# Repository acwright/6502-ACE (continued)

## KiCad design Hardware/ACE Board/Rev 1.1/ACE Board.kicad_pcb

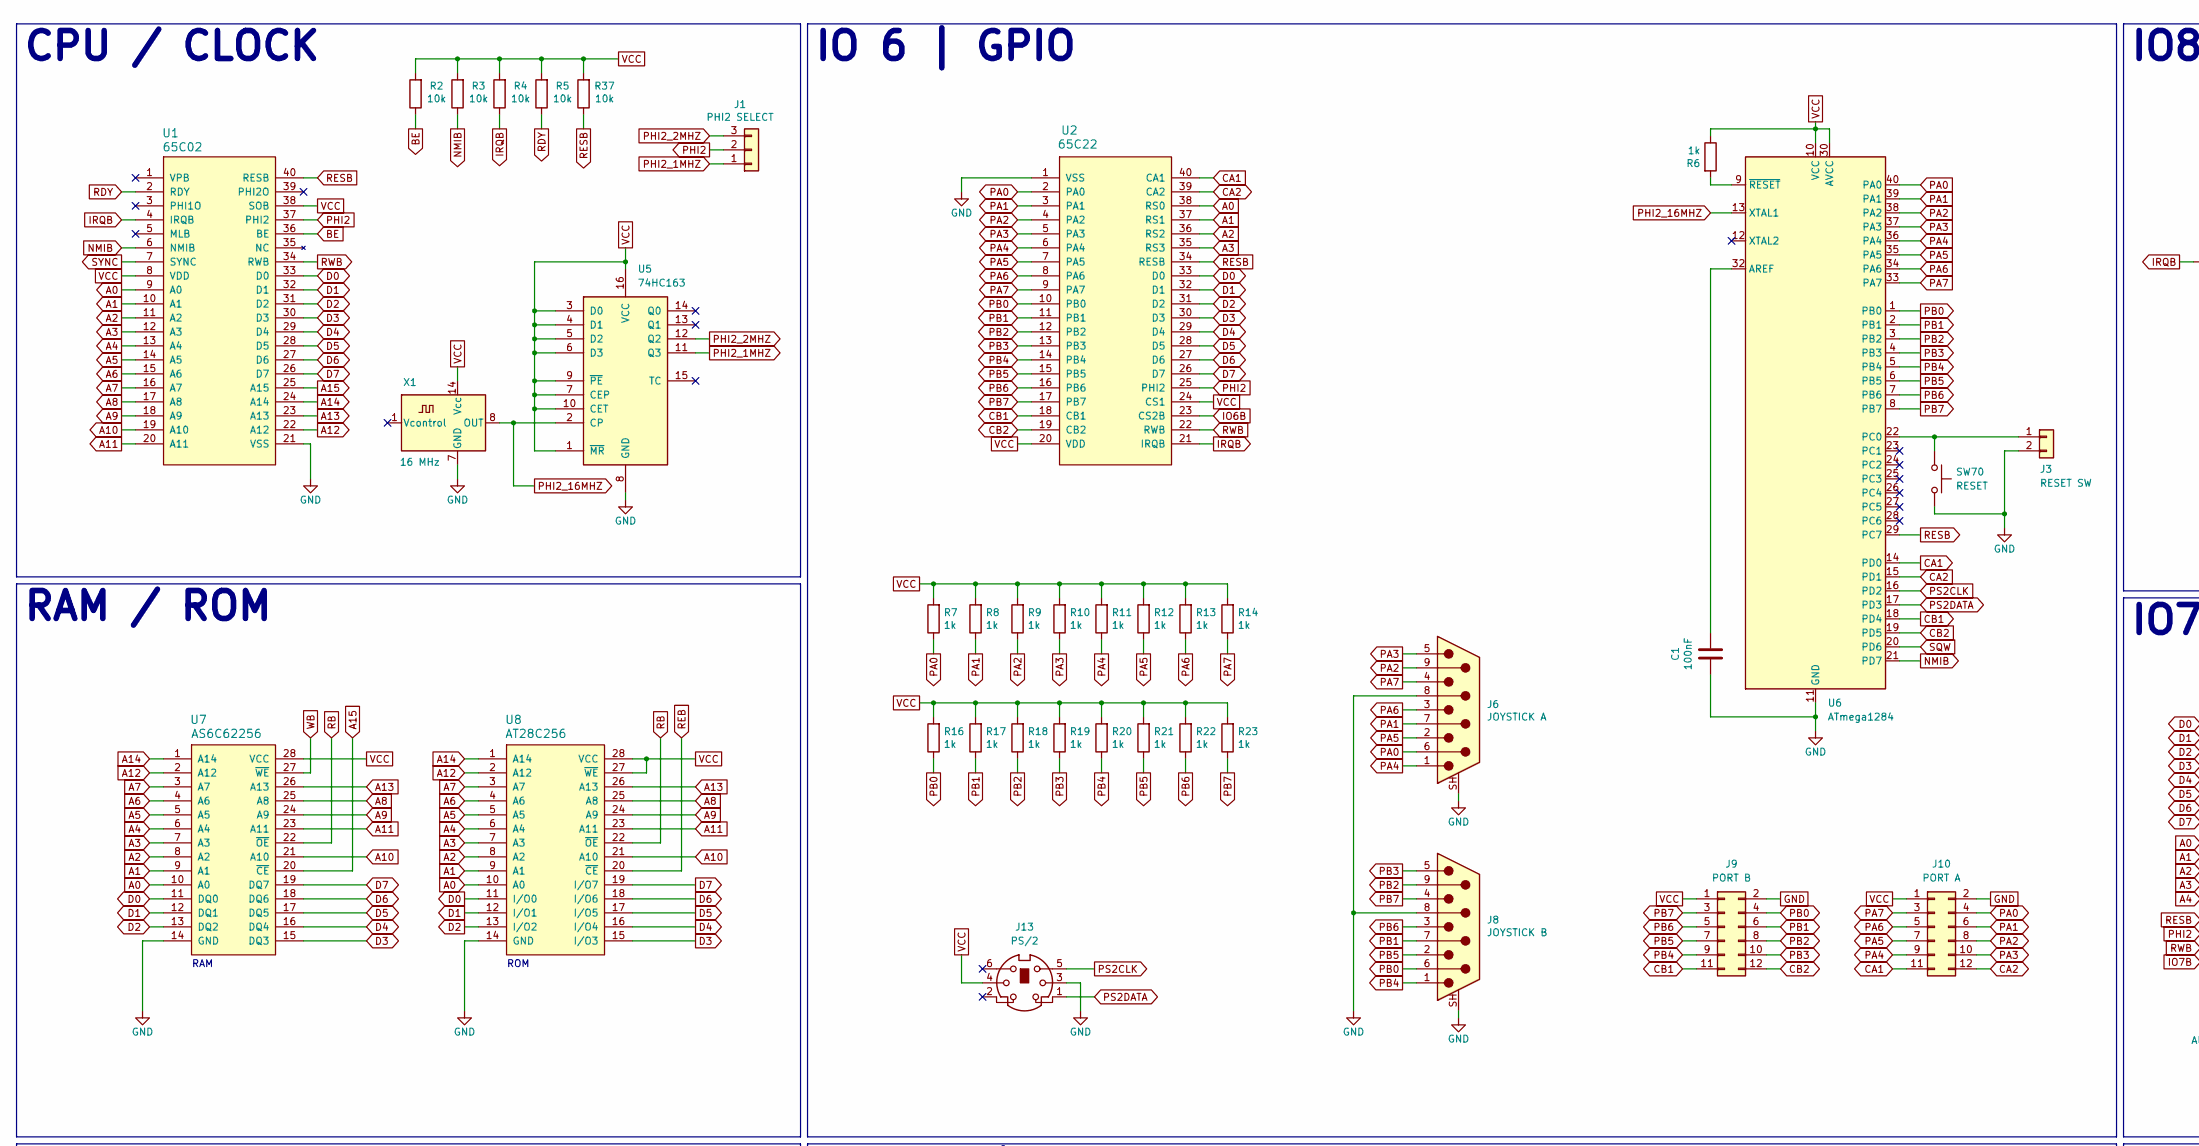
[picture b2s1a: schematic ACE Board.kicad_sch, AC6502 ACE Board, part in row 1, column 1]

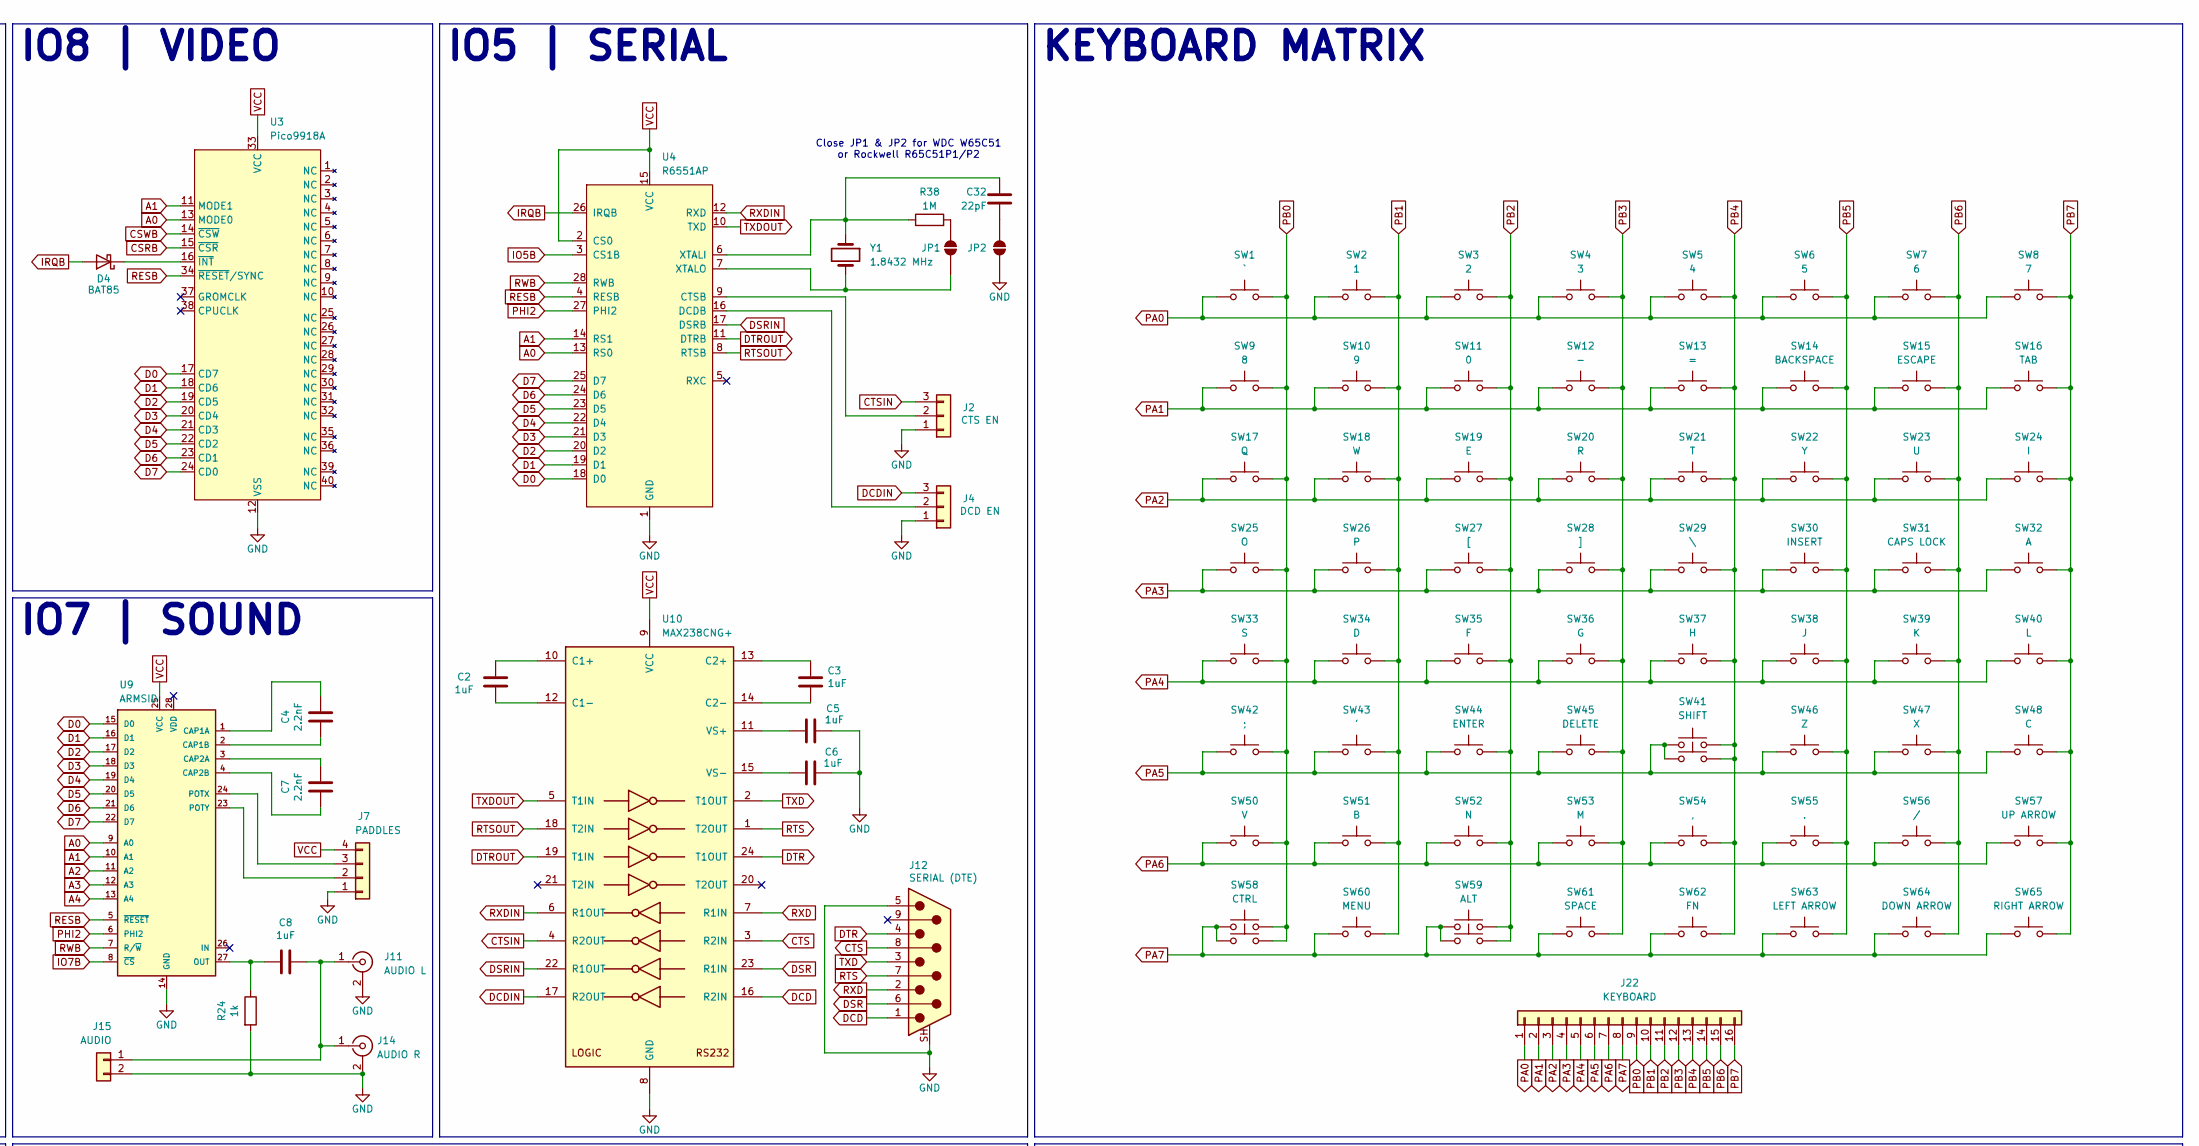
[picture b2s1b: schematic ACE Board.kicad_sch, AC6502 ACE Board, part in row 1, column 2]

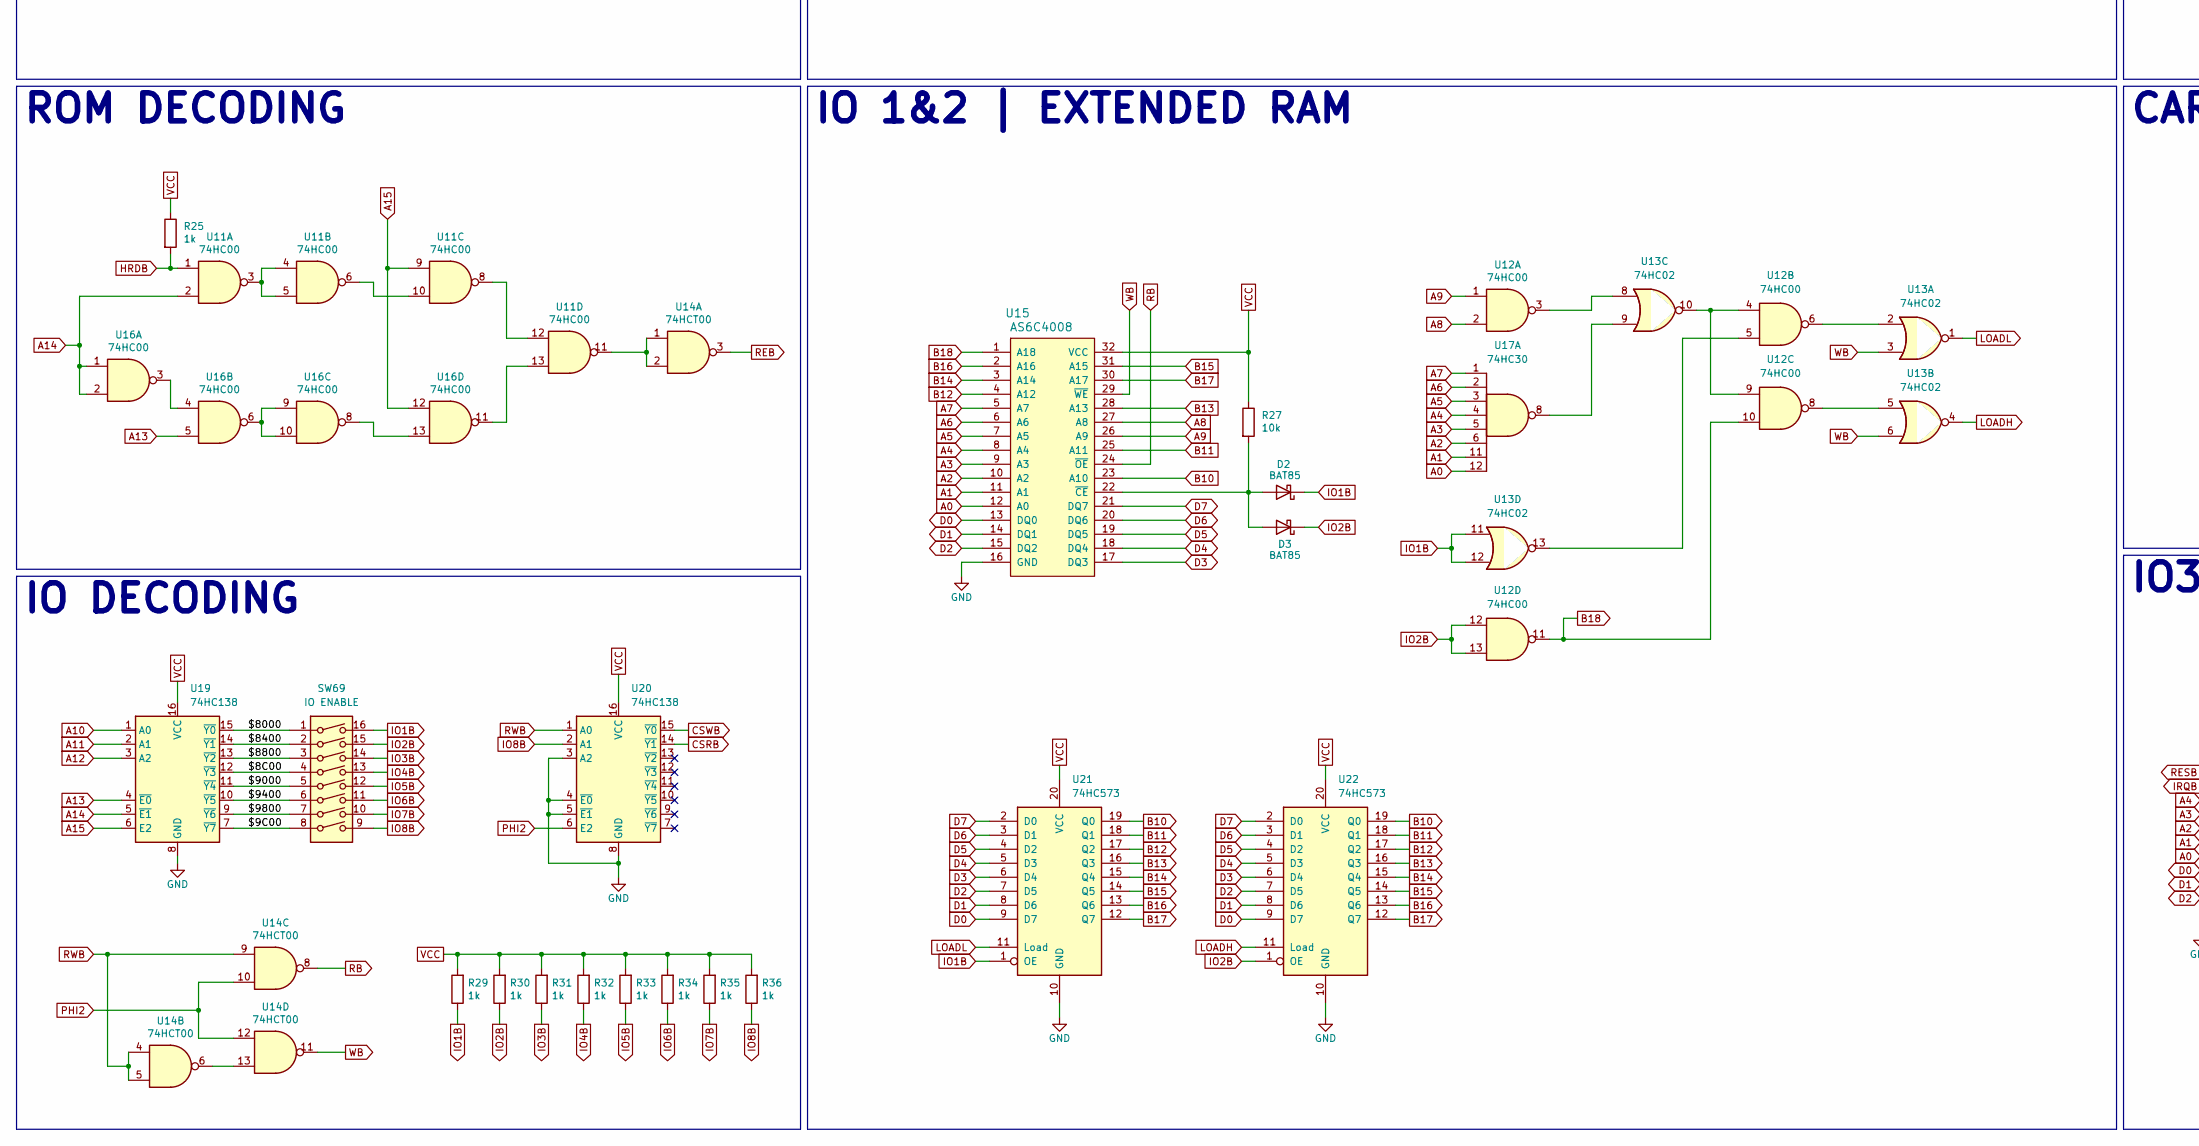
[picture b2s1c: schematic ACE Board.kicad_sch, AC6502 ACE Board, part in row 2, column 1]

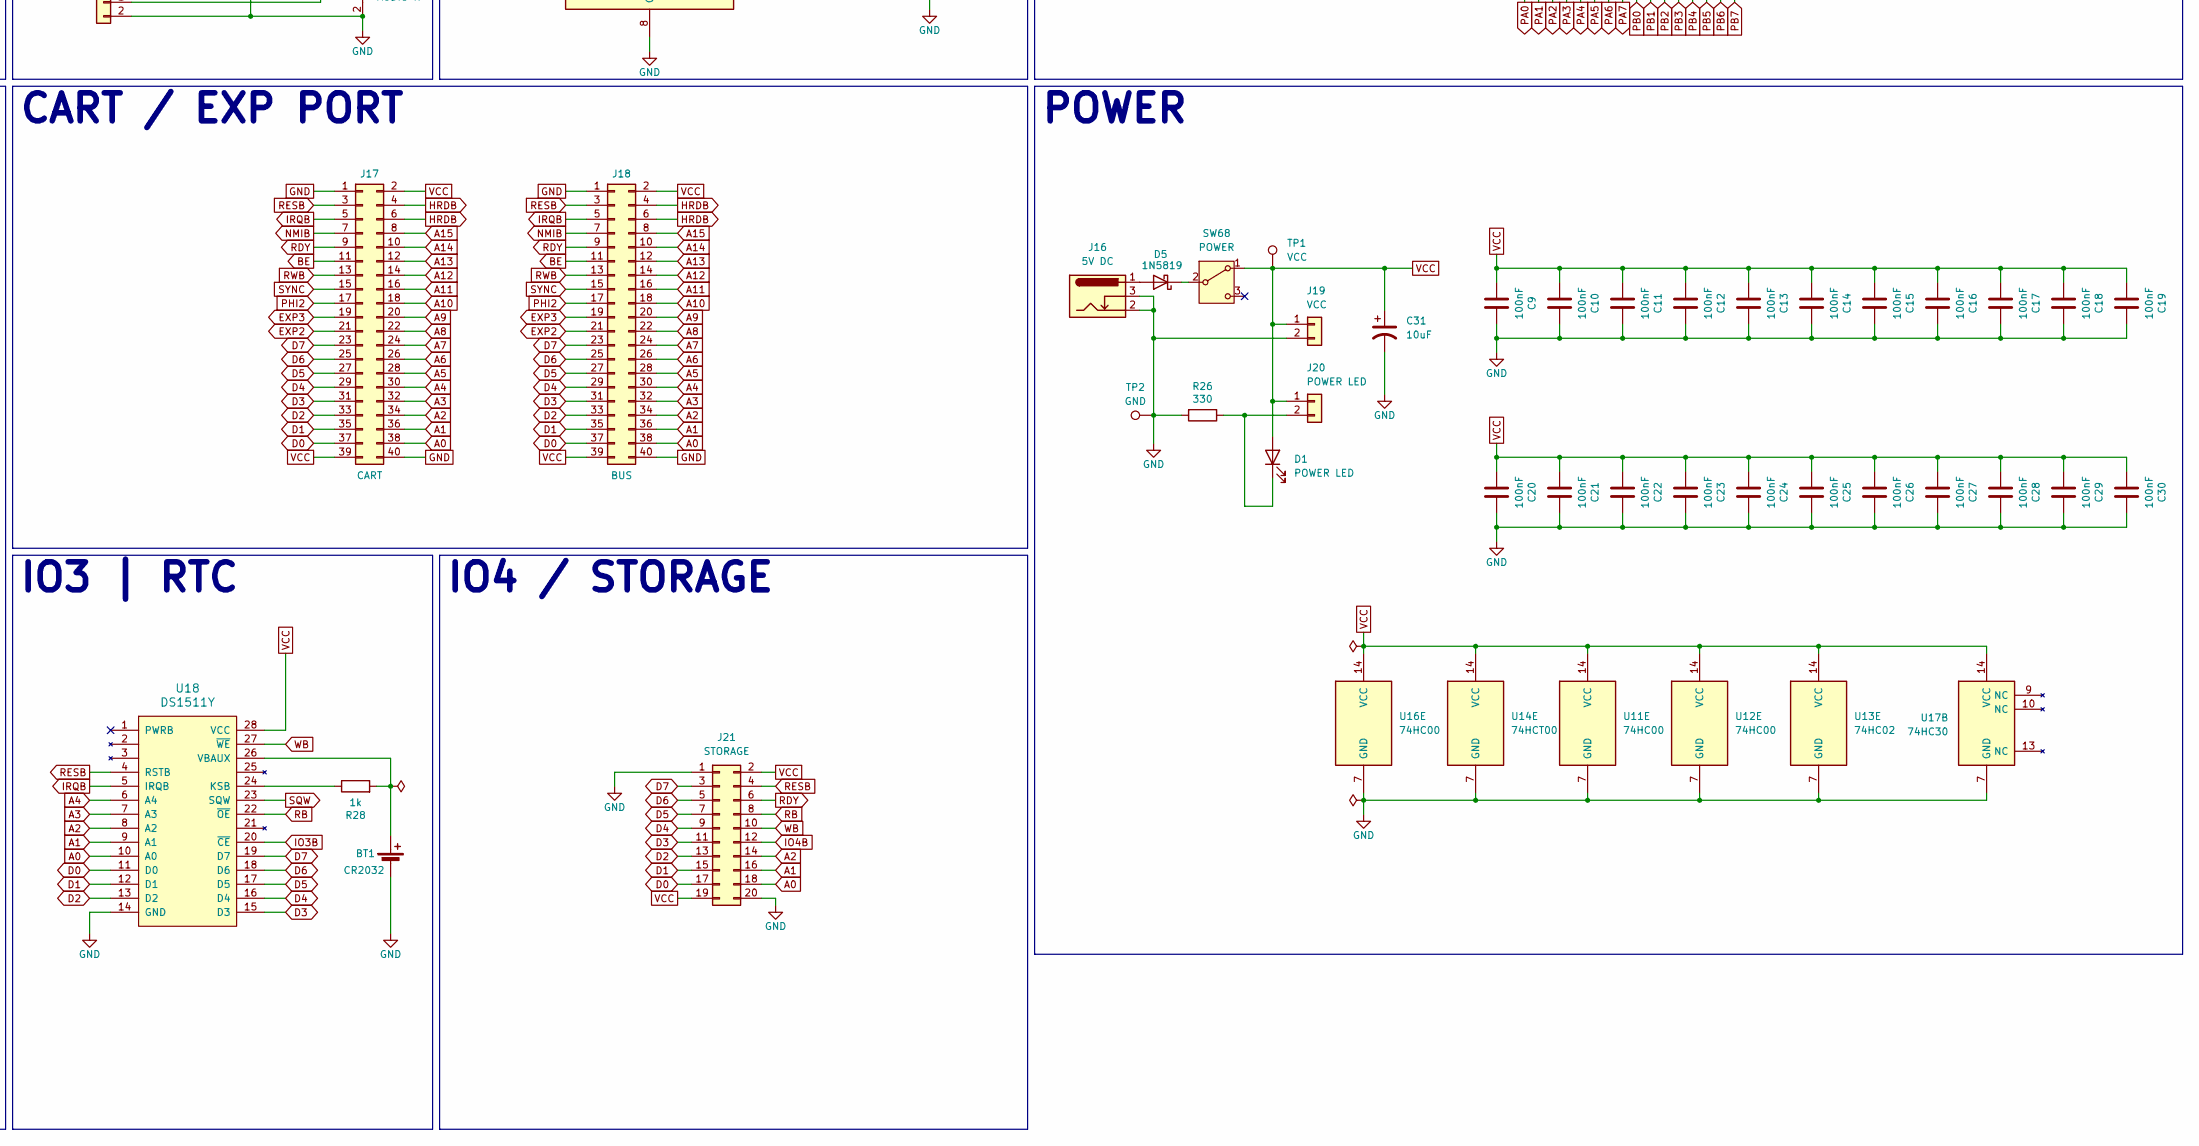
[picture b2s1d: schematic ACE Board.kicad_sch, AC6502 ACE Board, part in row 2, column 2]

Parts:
BT1: CR2032; CR2032 Holder Numbered; Digikey 343-BAT-HLD-001-THM-TRCT-ND
C1, C9, C10, C11, C12, C13, C14, C15, C16, C17, C18, C19, C20, C21, C22, C23, C24, C25, C26, C27, C28, C29, C30: 100nF; C_Disc_D5.0mm_W2.5mm_P2.50mm; Digikey 478-3187-ND
C2, C3, C5, C6, C8: 1uF; C_Disc_D5.0mm_W2.5mm_P2.50mm; Digikey 478-7667-ND
C4, C7: 2.2nF; C_Disc_D5.0mm_W2.5mm_P2.50mm; Digikey 478-11698-ND
C31: 10uF; CP_Radial_D4.0mm_P1.50mm; Digikey P14482-ND
C32: 22pF; C_Disc_D5.0mm_W2.5mm_P2.50mm; Digikey 478-4846-ND
D1: POWER LED; LED_D3.0mm; Digikey 732-5008-ND
D2, D3, D4: BAT85; D_DO-35_SOD27_P7.62mm_Horizontal; Digikey BAT85SCT-ND
D5: 1N5819; D_DO-41_SOD81_P10.16mm_Horizontal; Digikey 1N5819-E3/54GICT-ND
J1: PHI2 SELECT; PinHeader_1x03_P2.54mm_Vertical; Digikey S1011EC-40-ND
J2: CTS EN; PinHeader_1x03_P2.54mm_Vertical; Digikey S1011EC-40-ND
J3: RESET SW; PinHeader_1x02_P2.54mm_Vertical; Digikey S1011EC-40-ND
J4: DCD EN; PinHeader_1x03_P2.54mm_Vertical; Digikey S1011EC-40-ND
J6: JOYSTICK A; DSUB-9_Pins_Horizontal_P2.77x2.84mm_EdgePinOffset7.70mm_Hou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; Digikey 609-1481-ND
J7: PADDLES; PinHeader_1x04_P2.54mm_Vertical; Digikey S1011EC-40-ND
J8: JOYSTICK B; DSUB-9_Pins_Horizontal_P2.77x2.84mm_EdgePinOffset7.70mm_Hou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; Digikey 609-1481-ND
J9: PORT B; 6502 GPIO Connector; Digikey 2057-BHR-12-VUA-ND
J10: PORT A; 6502 GPIO Connector; Digikey 2057-BHR-12-VUA-ND
J11: AUDIO L; RCA Jack White; Digikey PJRAN1X1U02X-ND
J12: SERIAL (DTE); DSUB-9_Pins_Horizontal_P2.77x2.84mm_EdgePinOffset7.70mm_Hou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; Digikey 609-1481-ND
J13: PS/2; PS2 Jack; Mouser 806-KMDGX-6S-BS
J14: AUDIO R; RCA Jack White; Digikey PJRAN1X1U03X-ND
J15: AUDIO; PinHeader_1x02_P2.54mm_Vertical; Digikey S1011EC-40-ND
J16: 5V DC; BarrelJack_Horizontal; Digikey CP-102AH-ND
J17: CART; 6502 Card Slot; Digikey A31723-ND
J18: BUS; 6502 Bus Connector; Digikey 732-5401-ND
J19: VCC; PinHeader_1x02_P2.54mm_Vertical; Digikey S1011EC-40-ND
J20: POWER LED; PinHeader_1x02_P2.54mm_Vertical; Digikey S1011EC-40-ND
J21: STORAGE; PinSocket_2x10_P2.54mm_Horizontal; Digikey S5563-ND
J22: KEYBOARD; PinHeader_1x16_P2.00mm_Vertical; Digikey 2057-2PH1-16-UA-ND
JP1, JP2: SolderJumper_2_Open; SolderJumper-2_P1.3mm_Open_RoundedPad1.0x1.5mm
R2, R3, R4, R5, R27, R37: 10k; R_Axial_DIN0204_L3.6mm_D1.6mm_P5.08mm_Horizontal; Digikey 13-MFR-12FTF52-10KCT-ND
R6, R7, R8, R9, R10, R11, R12, R13, R14, R16, R17, R18, R19, R20, R21, R22, R23, R24, R25, R28, R29, R30, R31, R32, R33, R34, R35, R36: 1k; R_Axial_DIN0204_L3.6mm_D1.6mm_P5.08mm_Horizontal; Digikey 13-MFR-12FTF52-1KCT-ND
R26: 330; R_Axial_DIN0204_L3.6mm_D1.6mm_P5.08mm_Horizontal; Digikey 13-MFR-12FTF52-330RCT-ND
R38: 1M; R_Axial_DIN0204_L3.6mm_D1.6mm_P5.08mm_Horizontal; Digikey 13-MFR-12FTF52-1MCT-ND
SW1: `; SW_Cherry_MX_1.00u_PCB; Digikey 1644-MX2A-E1NA-ND
SW2: 1; SW_Cherry_MX_1.00u_PCB; Digikey 1644-MX2A-E1NA-ND
SW3: 2; SW_Cherry_MX_1.00u_PCB; Digikey 1644-MX2A-E1NA-ND
SW4: 3; SW_Cherry_MX_1.00u_PCB; Digikey 1644-MX2A-E1NA-ND
SW5: 4; SW_Cherry_MX_1.00u_PCB; Digikey 1644-MX2A-E1NA-ND
SW6: 5; SW_Cherry_MX_1.00u_PCB; Digikey 1644-MX2A-E1NA-ND
SW7: 6; SW_Cherry_MX_1.00u_PCB; Digikey 1644-MX2A-E1NA-ND
SW8: 7; SW_Cherry_MX_1.00u_PCB; Digikey 1644-MX2A-E1NA-ND
SW9: 8; SW_Cherry_MX_1.00u_PCB; Digikey 1644-MX2A-E1NA-ND
SW10: 9; SW_Cherry_MX_1.00u_PCB; Digikey 1644-MX2A-E1NA-ND
SW11: 0; SW_Cherry_MX_1.00u_PCB; Digikey 1644-MX2A-E1NA-ND
SW12: -; SW_Cherry_MX_1.00u_PCB; Digikey 1644-MX2A-E1NA-ND
SW13: =; SW_Cherry_MX_1.00u_PCB; Digikey 1644-MX2A-E1NA-ND
SW14: BACKSPACE; SW_Cherry_MX_2.00u_PCB; Digikey 1644-MX2A-E1NA-ND
SW15: ESCAPE; SW_Cherry_MX_1.00u_PCB; Digikey 1644-MX2A-E1NA-ND
SW16: TAB; SW_Cherry_MX_1.50u_PCB; Digikey 1644-MX2A-E1NA-ND
SW17: Q; SW_Cherry_MX_1.00u_PCB; Digikey 1644-MX2A-E1NA-ND
SW18: W; SW_Cherry_MX_1.00u_PCB; Digikey 1644-MX2A-E1NA-ND
SW19: E; SW_Cherry_MX_1.00u_PCB; Digikey 1644-MX2A-E1NA-ND
SW20: R; SW_Cherry_MX_1.00u_PCB; Digikey 1644-MX2A-E1NA-ND
SW21: T; SW_Cherry_MX_1.00u_PCB; Digikey 1644-MX2A-E1NA-ND
SW22: Y; SW_Cherry_MX_1.00u_PCB; Digikey 1644-MX2A-E1NA-ND
SW23: U; SW_Cherry_MX_1.00u_PCB; Digikey 1644-MX2A-E1NA-ND
SW24: I; SW_Cherry_MX_1.00u_PCB; Digikey 1644-MX2A-E1NA-ND
SW25: O; SW_Cherry_MX_1.00u_PCB; Digikey 1644-MX2A-E1NA-ND
SW26: P; SW_Cherry_MX_1.00u_PCB; Digikey 1644-MX2A-E1NA-ND
SW27: [; SW_Cherry_MX_1.00u_PCB; Digikey 1644-MX2A-E1NA-ND
SW28: ]; SW_Cherry_MX_1.00u_PCB; Digikey 1644-MX2A-E1NA-ND
SW29: \; SW_Cherry_MX_1.50u_PCB; Digikey 1644-MX2A-E1NA-ND
SW30: INSERT; SW_Cherry_MX_1.00u_PCB; Digikey 1644-MX2A-E1NA-ND
SW31: CAPS LOCK; SW_Cherry_MX_1.75u_PCB; Digikey 1644-MX2A-E1NA-ND
SW32: A; SW_Cherry_MX_1.00u_PCB; Digikey 1644-MX2A-E1NA-ND
SW33: S; SW_Cherry_MX_1.00u_PCB; Digikey 1644-MX2A-E1NA-ND
SW34: D; SW_Cherry_MX_1.00u_PCB; Digikey 1644-MX2A-E1NA-ND
SW35: F; SW_Cherry_MX_1.00u_PCB; Digikey 1644-MX2A-E1NA-ND
SW36: G; SW_Cherry_MX_1.00u_PCB; Digikey 1644-MX2A-E1NA-ND
SW37: H; SW_Cherry_MX_1.00u_PCB; Digikey 1644-MX2A-E1NA-ND
SW38: J; SW_Cherry_MX_1.00u_PCB; Digikey 1644-MX2A-E1NA-ND
SW39: K; SW_Cherry_MX_1.00u_PCB; Digikey 1644-MX2A-E1NA-ND
SW40: L; SW_Cherry_MX_1.00u_PCB; Digikey 1644-MX2A-E1NA-ND
SW41, SW49: SHIFT; SW_Cherry_MX_2.25u_PCB; Digikey 1644-MX2A-E1NA-ND
SW42: ;; SW_Cherry_MX_1.00u_PCB; Digikey 1644-MX2A-E1NA-ND
SW43: '; SW_Cherry_MX_1.00u_PCB; Digikey 1644-MX2A-E1NA-ND
SW44: ENTER; SW_Cherry_MX_2.25u_PCB; Digikey 1644-MX2A-E1NA-ND
SW45: DELETE; SW_Cherry_MX_1.00u_PCB; Digikey 1644-MX2A-E1NA-ND
SW46: Z; SW_Cherry_MX_1.00u_PCB; Digikey 1644-MX2A-E1NA-ND
SW47: X; SW_Cherry_MX_1.00u_PCB; Digikey 1644-MX2A-E1NA-ND
SW48: C; SW_Cherry_MX_1.00u_PCB; Digikey 1644-MX2A-E1NA-ND
SW50: V; SW_Cherry_MX_1.00u_PCB; Digikey 1644-MX2A-E1NA-ND
SW51: B; SW_Cherry_MX_1.00u_PCB; Digikey 1644-MX2A-E1NA-ND
SW52: N; SW_Cherry_MX_1.00u_PCB; Digikey 1644-MX2A-E1NA-ND
SW53: M; SW_Cherry_MX_1.00u_PCB; Digikey 1644-MX2A-E1NA-ND
SW54: ,; SW_Cherry_MX_1.00u_PCB; Digikey 1644-MX2A-E1NA-ND
SW55: .; SW_Cherry_MX_1.00u_PCB; Digikey 1644-MX2A-E1NA-ND
SW56: /; SW_Cherry_MX_1.00u_PCB; Digikey 1644-MX2A-E1NA-ND
SW57: UP ARROW; SW_Cherry_MX_1.00u_PCB; Digikey 1644-MX2A-E1NA-ND
SW58, SW66: CTRL; SW_Cherry_MX_1.25u_PCB; Digikey 1644-MX2A-E1NA-ND
SW59, SW67: ALT; SW_Cherry_MX_1.25u_PCB; Digikey 1644-MX2A-E1NA-ND
SW60: MENU; SW_Cherry_MX_1.00u_PCB; Digikey 1644-MX2A-E1NA-ND
SW61: SPACE; SW_Cherry_MX_6.25u_PCB; Digikey 1644-MX2A-E1NA-ND
SW62: FN; SW_Cherry_MX_1.25u_PCB; Digikey 1644-MX2A-E1NA-ND
SW63: LEFT ARROW; SW_Cherry_MX_1.00u_PCB; Digikey 1644-MX2A-E1NA-ND
SW64: DOWN ARROW; SW_Cherry_MX_1.00u_PCB; Digikey 1644-MX2A-E1NA-ND
SW65: RIGHT ARROW; SW_Cherry_MX_1.00u_PCB; Digikey 1644-MX2A-E1NA-ND
SW68: POWER; Power Switch; Digikey EG4326-ND
SW69: IO ENABLE; SW_DIP_SPSTx08_Slide_9.78x22.5mm_W7.62mm_P2.54mm; Digikey CT2068-ND
SW70: RESET; SW_PUSH_6mm; Digikey 2223-TS02-66-50-BK-160-LCR-D-ND
TP1: VCC; TestPoint_Pad_2.5x2.5mm
TP2: GND; TestPoint_Pad_2.5x2.5mm
U1: 65C02; DIP-40_W15.24mm_Socket_LongPads; Mouser 955-W65C02S6TPG-14
U2: 65C22; DIP-40_W15.24mm_Socket_LongPads; Mouser 955-W65C22N6TPG-14
U3: Pico9918A; DIP-40_W15.24mm_Socket_LongPads
U4: R6551AP; DIP-28_W15.24mm_Socket_LongPads
U5: 74HC163; DIP-16_W7.62mm_Socket_LongPads; Digikey 296-8246-5-ND
U6: ATmega1284; DIP-40_W15.24mm_Socket_LongPads; Digikey ATMEGA1284-PU-ND
U7: AS6C62256; DIP-28_W15.24mm_Socket_LongPads; Digikey 1450-1033-ND
U8: AT28C256; DIP_Socket-28_W11.9mm_W12.7mm_W15.24mm_W17.78mm_W18.5mm_3M_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; Digikey AT28C256-15PU-ND
U9: ARMSID; DIP-28_W15.24mm_Socket_LongPads
U10: MAX238CNG+; DIP-24_W7.62mm_Socket_LongPads; Digikey MAX238CNG+-ND
U11, U12, U16: 74HC00; DIP-14_W7.62mm_Socket_LongPads; Digikey 296-1563-5-ND
U13: 74HC02; DIP-14_W7.62mm_Socket_LongPads; Digikey 296-1564-5-ND
U14: 74HCT00; DIP-14_W7.62mm_Socket_LongPads; Digikey 296-1603-5-ND
U15: AS6C4008; DIP-32_W15.24mm_Socket_LongPads; Digikey 1450-1027-ND
U17: 74HC30; DIP-14_W7.62mm_Socket_LongPads; Mouser 595-CD74HC30E
U18: DS1511Y; DIP-28_W15.24mm_Socket_LongPads; Digikey DS1511Y+-ND
U19, U20: 74HC138; DIP-16_W7.62mm_Socket_LongPads; Digikey 296-1575-5-ND
U21, U22: 74HC573; DIP-20_W7.62mm_Socket_LongPads; Digikey 296-12815-5-ND
X1: 16 MHz; Oscillator_DIP-14; Digikey X947-ND
Y1: 1.8432 MHz; Crystal_HC49-U_Vertical; Digikey 535-9009-ND

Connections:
/$8C00: SW69.4, U19.12 (~Y3)
/$9C00: SW69.8, U19.7 (~Y7)
/$8000: SW69.1, U19.15 (~Y0)
/$8400: SW69.2, U19.14 (~Y1)
/$8800: SW69.3, U19.13 (~Y2)
/$9000: SW69.5, U19.11 (~Y4)
/$9400: SW69.6, U19.10 (~Y5)
/$9800: SW69.7, U19.9 (~Y6)
A0: J17.38, J18.38, J21.18, U1.9 (A0), U2.38 (RS0), U3.13 (MODE0), U4.13 (RS0), U7.10 (A0), U8.10 (A0), U9.9 (A0), U15.12 (A0), U17.12, U18.10 (A0)
A1: J17.36, J18.36, J21.16, U1.10 (A1), U2.37 (RS1), U3.11 (MODE1), U4.14 (RS1), U7.9 (A1), U8.9 (A1), U9.10 (A1), U15.11 (A1), U17.11, U18.9 (A1)
A2: J17.34, J18.34, J21.14, U1.11 (A2), U2.36 (RS2), U7.8 (A2), U8.8 (A2), U9.11 (A2), U15.10 (A2), U17.6, U18.8 (A2)
A3: J17.32, J18.32, U1.12 (A3), U2.35 (RS3), U7.7 (A3), U8.7 (A3), U9.12 (A3), U15.9 (A3), U17.5, U18.7 (A3)
A4: J17.30, J18.30, U1.13 (A4), U7.6 (A4), U8.6 (A4), U9.13 (A4), U15.8 (A4), U17.4, U18.6 (A4)
A5: J17.28, J18.28, U1.14 (A5), U7.5 (A5), U8.5 (A5), U15.7 (A5), U17.3
A6: J17.26, J18.26, U1.15 (A6), U7.4 (A6), U8.4 (A6), U15.6 (A6), U17.2
A7: J17.24, J18.24, U1.16 (A7), U7.3 (A7), U8.3 (A7), U15.5 (A7), U17.1
A8: J17.22, J18.22, U1.17 (A8), U7.25 (A8), U8.25 (A8), U12.2, U15.27 (A8)
A9: J17.20, J18.20, U1.18 (A9), U7.24 (A9), U8.24 (A9), U12.1, U15.26 (A9)
A10: J17.18, J18.18, U1.19 (A10), U7.21 (A10), U8.21 (A10), U19.1 (A0)
A11: J17.16, J18.16, U1.20 (A11), U7.23 (A11), U8.23 (A11), U19.2 (A1)
A12: J17.14, J18.14, U1.22 (A12), U7.2 (A12), U8.2 (A12), U19.3 (A2)
A13: J17.12, J18.12, U1.23 (A13), U7.26 (A13), U8.26 (A13), U16.5, U19.4 (~E0)
A14: J17.10, J18.10, U1.24 (A14), U7.1 (A14), U8.1 (A14), U11.2, U16.1, U16.2, U19.5 (~E1)
A15: J17.8, J18.8, U1.25 (A15), U7.20 (~CE), U11.9, U16.12, U19.6 (E2)
B10: U15.23 (A10), U21.19 (Q0), U22.19 (Q0)
B11: U15.25 (A11), U21.18 (Q1), U22.18 (Q1)
B12: U15.4 (A12), U21.17 (Q2), U22.17 (Q2)
B13: U15.28 (A13), U21.16 (Q3), U22.16 (Q3)
B14: U15.3 (A14), U21.15 (Q4), U22.15 (Q4)
B15: U15.31 (A15), U21.14 (Q5), U22.14 (Q5)
B16: U15.2 (A16), U21.13 (Q6), U22.13 (Q6)
B17: U15.30 (A17), U21.12 (Q7), U22.12 (Q7)
B18: U12.10, U12.11, U15.1 (A18)
BE: J17.11, J18.11, R2.1, U1.36 (BE)
CA1: J10.11, U2.40 (CA1), U6.14 (PD0)
CA2: J10.12, U2.39 (CA2), U6.15 (PD1)
CB1: J9.11, U2.18 (CB1), U6.18 (PD4)
CB2: J9.12, U2.19 (CB2), U6.19 (PD5)
CSRB: U3.15 (~CSR), U20.14 (~Y1)
CSWB: U3.14 (~CSW), U20.15 (~Y0)
CTS: J12.8, U10.3 (R2IN)
CTSIN: J2.3, U10.4 (R2OUT)
D0: J17.37, J18.37, J21.17, U1.33 (D0), U2.33 (D0), U3.17 (CD7), U4.18 (D0), U7.11 (DQ0), U8.11 (I/O0), U9.15 (D0), U15.13 (DQ0), U18.11 (D0), U21.9 (D7), U22.9 (D7)
D1: J17.35, J18.35, J21.15, U1.32 (D1), U2.32 (D1), U3.18 (CD6), U4.19 (D1), U7.12 (DQ1), U8.12 (I/O1), U9.16 (D1), U15.14 (DQ1), U18.12 (D1), U21.8 (D6), U22.8 (D6)
D2: J17.33, J18.33, J21.13, U1.31 (D2), U2.31 (D2), U3.19 (CD5), U4.20 (D2), U7.13 (DQ2), U8.13 (I/O2), U9.17 (D2), U15.15 (DQ2), U18.13 (D2), U21.7 (D5), U22.7 (D5)
D3: J17.31, J18.31, J21.11, U1.30 (D3), U2.30 (D3), U3.20 (CD4), U4.21 (D3), U7.15 (DQ3), U8.15 (I/O3), U9.18 (D3), U15.17 (DQ3), U18.15 (D3), U21.6 (D4), U22.6 (D4)
D4: J17.29, J18.29, J21.9, U1.29 (D4), U2.29 (D4), U3.21 (CD3), U4.22 (D4), U7.16 (DQ4), U8.16 (I/O4), U9.19 (D4), U15.18 (DQ4), U18.16 (D4), U21.5 (D3), U22.5 (D3)
D5: J17.27, J18.27, J21.7, U1.28 (D5), U2.28 (D5), U3.22 (CD2), U4.23 (D5), U7.17 (DQ5), U8.17 (I/O5), U9.20 (D5), U15.19 (DQ5), U18.17 (D5), U21.4 (D2), U22.4 (D2)
D6: J17.25, J18.25, J21.5, U1.27 (D6), U2.27 (D6), U3.23 (CD1), U4.24 (D6), U7.18 (DQ6), U8.18 (I/O6), U9.21 (D6), U15.20 (DQ6), U18.18 (D6), U21.3 (D1), U22.3 (D1)
D7: J17.23, J18.23, J21.3, U1.26 (D7), U2.26 (D7), U3.24 (CD0), U4.25 (D7), U7.19 (DQ7), U8.19 (I/O7), U9.22 (D7), U15.21 (DQ7), U18.19 (D7), U21.2 (D0), U22.2 (D0)
DCD: J12.1, U10.16 (R2IN)
DCDIN: J4.3, U10.17 (R2OUT)
DSR: J12.6, U10.23 (R1IN)
DSRIN: U4.17 (DSRB), U10.22 (R1OUT)
DTR: J12.4, U10.24 (T1OUT)
DTROUT: U4.11 (DTRB), U10.19 (T1IN)
EXP2: J17.21, J18.21
EXP3: J17.19, J18.19
GND: BT1.2 (-), C1.1, C5.2, C6.2, C9.2, C10.2, C11.2, C12.2, C13.2, C14.2, C15.2, C16.2, C17.2, C18.2, C19.2, C20.2, C21.2, C22.2, C23.2, C24.2, C25.2, C26.2, C27.2, C28.2, C29.2, C30.2, C31.2, J2.1, J3.2, J4.1, J6.8, J6.SH (PAD), J7.1, J8.8, J8.SH (PAD), J9.2, J10.2, J11.2 (Ext), J12.5, J12.SH (PAD), J13.3, J14.2 (Ext), J15.2, J16.2, J16.3, J17.1, J17.40, J18.1, J18.40, J19.2, J21.1, J21.20, JP2.1 (A), R24.2, R26.2, SW70.2, TP2.1 (1_1), U1.21 (VSS), U2.1 (VSS), U3.12 (VSS), U4.1 (GND), U5.8 (GND), U6.11 (GND), U6.31 (GND), U7.14 (GND), U8.14 (GND), U9.14 (GND), U10.8 (GND), U11.7 (GND), U12.7 (GND), U13.7 (GND), U14.7 (GND), U15.16 (GND), U16.7 (GND), U17.7 (GND), U18.14 (GND), U19.8 (GND), U20.3 (A2), U20.4 (~E0), U20.5 (~E1), U20.8 (GND), U21.10 (GND), U22.10 (GND), X1.7 (GND)
HRDB: J17.4, J17.6, J18.4, J18.6, R25.2, U11.1
IO1B: D2.1 (K), R29.1, SW69.16, U13.11, U13.12, U21.1 (OE)
IO2B: D3.1 (K), R30.1, SW69.15, U12.12, U12.13, U22.1 (OE)
IO3B: R31.1, SW69.14, U18.20 (~CE)
IO4B: J21.12, R32.1, SW69.13
IO5B: R33.1, SW69.12, U4.3 (CS1B)
IO6B: R34.1, SW69.11, U2.23 (CS2B)
IO7B: R35.1, SW69.10, U9.8 (~CS)
IO8B: R36.1, SW69.9, U20.2 (A1)
IRQB: D4.2 (A), J17.5, J18.5, R4.1, U1.4 (IRQB), U2.21 (IRQB), U4.26 (IRQB), U18.5 (IRQB)
LOADH: U13.4, U22.11 (Load)
LOADL: U13.1, U21.11 (Load)
NMIB: J17.7, J18.7, R3.1, U1.6 (NMIB), U6.21 (PD7)
unnamed: BT1.1 (+), R28.2, U18.26 (VBAUX)
unnamed: D1.1 (K), J20.2, R26.1
unnamed: D2.2 (A), D3.2 (A), R27.2, U15.22 (~CE)
unnamed: D4.1 (K), U3.16 (~INT)
unnamed: D5.2 (A), J16.1
unnamed: D5.1 (K), SW68.2 (B)
unnamed: J2.2, U4.9 (CTSB)
unnamed: J3.1, SW70.1, U6.22 (PC0)
unnamed: J4.2, U4.16 (DCDB)
unnamed: J7.2, U9.23 (POTY)
unnamed: J7.3, U9.24 (POTX)
unnamed: C8.2, J11.1 (In), J14.1 (In), J15.1
unnamed: JP1.1 (A), U4.7 (XTALO), Y1.2
unnamed: JP1.2 (B), R38.2
unnamed: C32.2, JP2.2 (B)
unnamed: C32.1, R38.1, U4.6 (XTALI), Y1.1
unnamed: C1.2, U6.32 (AREF)
unnamed: R6.2, U6.9 (~RESET)
unnamed: C4.2, U9.1 (CAP1A)
unnamed: C4.1, U9.2 (CAP1B)
unnamed: C7.2, U9.3 (CAP2A)
unnamed: C7.1, U9.4 (CAP2B)
unnamed: C8.1, R24.1, U9.27 (OUT)
unnamed: C2.1, U10.10 (C1+)
unnamed: C2.2, U10.12 (C1-)
unnamed: C3.1, U10.13 (C2+)
unnamed: C3.2, U10.14 (C2-)
unnamed: C5.1, U10.11 (VS+)
unnamed: C6.1, U10.15 (VS-)
unnamed: U11.3, U11.4, U11.5
unnamed: U11.6, U11.10
unnamed: U11.11, U14.1, U14.2
unnamed: U11.8, U11.12
unnamed: U11.13, U16.11
unnamed: U12.3, U13.8
unnamed: U12.4, U12.9, U13.10
unnamed: U12.5, U13.13
unnamed: U12.6, U13.2
unnamed: U12.8, U13.5
unnamed: U13.9, U17.8
unnamed: U14.6, U14.13
unnamed: U16.3, U16.4
unnamed: U16.6, U16.9, U16.10
unnamed: U16.8, U16.13
unnamed: R28.1, U18.24 (KSB)
PA0: J6.6, J10.4, J22.1, R7.1, SW1.1, SW2.1, SW3.1, SW4.1, SW5.1, SW6.1, SW7.1, SW8.1, U2.2 (PA0), U6.40 (PA0)
PA1: J6.7, J10.6, J22.2, R8.1, SW9.1, SW10.1, SW11.1, SW12.1, SW13.1, SW14.1, SW15.1, SW16.1, U2.3 (PA1), U6.39 (PA1)
PA2: J6.9, J10.8, J22.3, R9.1, SW17.1, SW18.1, SW19.1, SW20.1, SW21.1, SW22.1, SW23.1, SW24.1, U2.4 (PA2), U6.38 (PA2)
PA3: J6.5, J10.10, J22.4, R10.1, SW25.1, SW26.1, SW27.1, SW28.1, SW29.1, SW30.1, SW31.1, SW32.1, U2.5 (PA3), U6.37 (PA3)
PA4: J6.1, J10.9, J22.5, R11.1, SW33.1, SW34.1, SW35.1, SW36.1, SW37.1, SW38.1, SW39.1, SW40.1, U2.6 (PA4), U6.36 (PA4)
PA5: J6.2, J10.7, J22.6, R12.1, SW41.1, SW42.1, SW43.1, SW44.1, SW45.1, SW46.1, SW47.1, SW48.1, SW49.1, U2.7 (PA5), U6.35 (PA5)
PA6: J6.3, J10.5, J22.7, R13.1, SW50.1, SW51.1, SW52.1, SW53.1, SW54.1, SW55.1, SW56.1, SW57.1, U2.8 (PA6), U6.34 (PA6)
PA7: J6.4, J10.3, J22.8, R14.1, SW58.1, SW59.1, SW60.1, SW61.1, SW62.1, SW63.1, SW64.1, SW65.1, SW66.1, SW67.1, U2.9 (PA7), U6.33 (PA7)
PB0: J8.6, J9.4, J22.9, R16.1, SW1.2, SW9.2, SW17.2, SW25.2, SW33.2, SW42.2, SW50.2, SW58.2, SW66.2, U2.10 (PB0), U6.1 (PB0)
PB1: J8.7, J9.6, J22.10, R17.1, SW2.2, SW10.2, SW18.2, SW26.2, SW34.2, SW43.2, SW51.2, SW60.2, U2.11 (PB1), U6.2 (PB1)
PB2: J8.9, J9.8, J22.11, R18.1, SW3.2, SW11.2, SW19.2, SW27.2, SW35.2, SW44.2, SW52.2, SW59.2, SW67.2, U2.12 (PB2), U6.3 (PB2)
PB3: J8.5, J9.10, J22.12, R19.1, SW4.2, SW12.2, SW20.2, SW28.2, SW36.2, SW45.2, SW53.2, SW61.2, U2.13 (PB3), U6.4 (PB3)
PB4: J8.1, J9.9, J22.13, R20.1, SW5.2, SW13.2, SW21.2, SW29.2, SW37.2, SW41.2, SW49.2, SW54.2, SW62.2, U2.14 (PB4), U6.5 (PB4)
PB5: J8.2, J9.7, J22.14, R21.1, SW6.2, SW14.2, SW22.2, SW30.2, SW38.2, SW46.2, SW55.2, SW63.2, U2.15 (PB5), U6.6 (PB5)
PB6: J8.3, J9.5, J22.15, R22.1, SW7.2, SW15.2, SW23.2, SW31.2, SW39.2, SW47.2, SW56.2, SW64.2, U2.16 (PB6), U6.7 (PB6)
PB7: J8.4, J9.3, J22.16, R23.1, SW8.2, SW16.2, SW24.2, SW32.2, SW40.2, SW48.2, SW57.2, SW65.2, U2.17 (PB7), U6.8 (PB7)
PHI2: J1.2, J17.17, J18.17, U1.37 (PHI2), U2.25 (PHI2), U4.27 (PHI2), U9.6 (PHI2), U14.10, U14.12, U20.6 (E2)
PHI2_1MHZ: J1.1, U5.11 (Q3)
PHI2_2MHZ: J1.3, U5.12 (Q2)
PHI2_16MHZ: U5.2 (CP), U6.13 (XTAL1), X1.8 (OUT)
PS2CLK: J13.5, U6.16 (PD2)
PS2DATA: J13.1, U6.17 (PD3)
RB: J21.8, U7.22 (~OE), U8.22 (~OE), U14.8, U15.24 (~OE), U18.22 (~OE)
RDY: J17.9, J18.9, J21.6, R5.1, U1.2 (RDY)
REB: U8.20 (~CE), U14.3
RESB: J17.3, J18.3, J21.4, R37.1, U1.40 (RESB), U2.34 (RESB), U3.34 (~RESET/SYNC), U4.4 (RESB), U6.29 (PC7), U9.5 (~RESET), U18.4 (RSTB)
RTS: J12.7, U10.1 (T2OUT)
RTSOUT: U4.8 (RTSB), U10.18 (T2IN)
RWB: J17.13, J18.13, U1.34 (RWB), U2.22 (RWB), U4.28 (RWB), U9.7 (R/~W), U14.4, U14.5, U14.9, U20.1 (A0)
RXD: J12.2, U10.7 (R1IN)
RXDIN: U4.12 (RXD), U10.6 (R1OUT)
SQW: U6.20 (PD6), U18.23 (SQW)
SYNC: J17.15, J18.15, U1.7 (SYNC)
TXD: J12.3, U10.2 (T1OUT)
TXDOUT: U4.10 (TXD), U10.5 (T1IN)
VCC: C9.1, C10.1, C11.1, C12.1, C13.1, C14.1, C15.1, C16.1, C17.1, C18.1, C19.1, C20.1, C21.1, C22.1, C23.1, C24.1, C25.1, C26.1, C27.1, C28.1, C29.1, C30.1, C31.1, D1.2 (A), J7.4, J9.1, J10.1, J13.4, J17.2, J17.39, J18.2, J18.39, J19.1, J20.1, J21.2, J21.19, R2.2, R3.2, R4.2, R5.2, R6.1, R7.2, R8.2, R9.2, R10.2, R11.2, R12.2, R13.2, R14.2, R16.2, R17.2, R18.2, R19.2, R20.2, R21.2, R22.2, R23.2, R25.1, R27.1, R29.2, R30.2, R31.2, R32.2, R33.2, R34.2, R35.2, R36.2, R37.2, SW68.1 (A), TP1.1 (1_1), U1.8 (VDD), U1.38 (SOB), U2.20 (VDD), U2.24 (CS1), U3.33 (VCC), U4.2 (CS0), U4.15 (VCC), U5.1 (~MR), U5.3 (D0), U5.4 (D1), U5.5 (D2), U5.6 (D3), U5.7 (CEP), U5.9 (~PE), U5.10 (CET), U5.16 (VCC), U6.10 (VCC), U6.30 (AVCC), U7.28 (VCC), U8.27 (~WE), U8.28 (VCC), U9.25 (VCC), U10.9 (VCC), U11.14 (VCC), U12.14 (VCC), U13.14 (VCC), U14.14 (VCC), U15.32 (VCC), U16.14 (VCC), U17.14 (VCC), U18.28 (VCC), U19.16 (VCC), U20.16 (VCC), U21.20 (VCC), U22.20 (VCC), X1.14 (Vcc)
WB: J21.10, U7.27 (~WE), U13.3, U13.6, U14.11, U15.29 (~WE), U18.27 (~WE)

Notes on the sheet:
ROM
Close JP1 & JP2 for WDC W65C51 or Rockwell R65C51P1/P2
RAM
IO4 / STORAGE
RAM / ROM
POWER
IO7 | SOUND
IO5 | SERIAL
IO8 | VIDEO
ROM DECODING
IO DECODING
IO 6 | GPIO
CART / EXP PORT
IO3 | RTC
CPU / CLOCK
IO 1&2 | EXTENDED RAM
KEYBOARD MATRIX

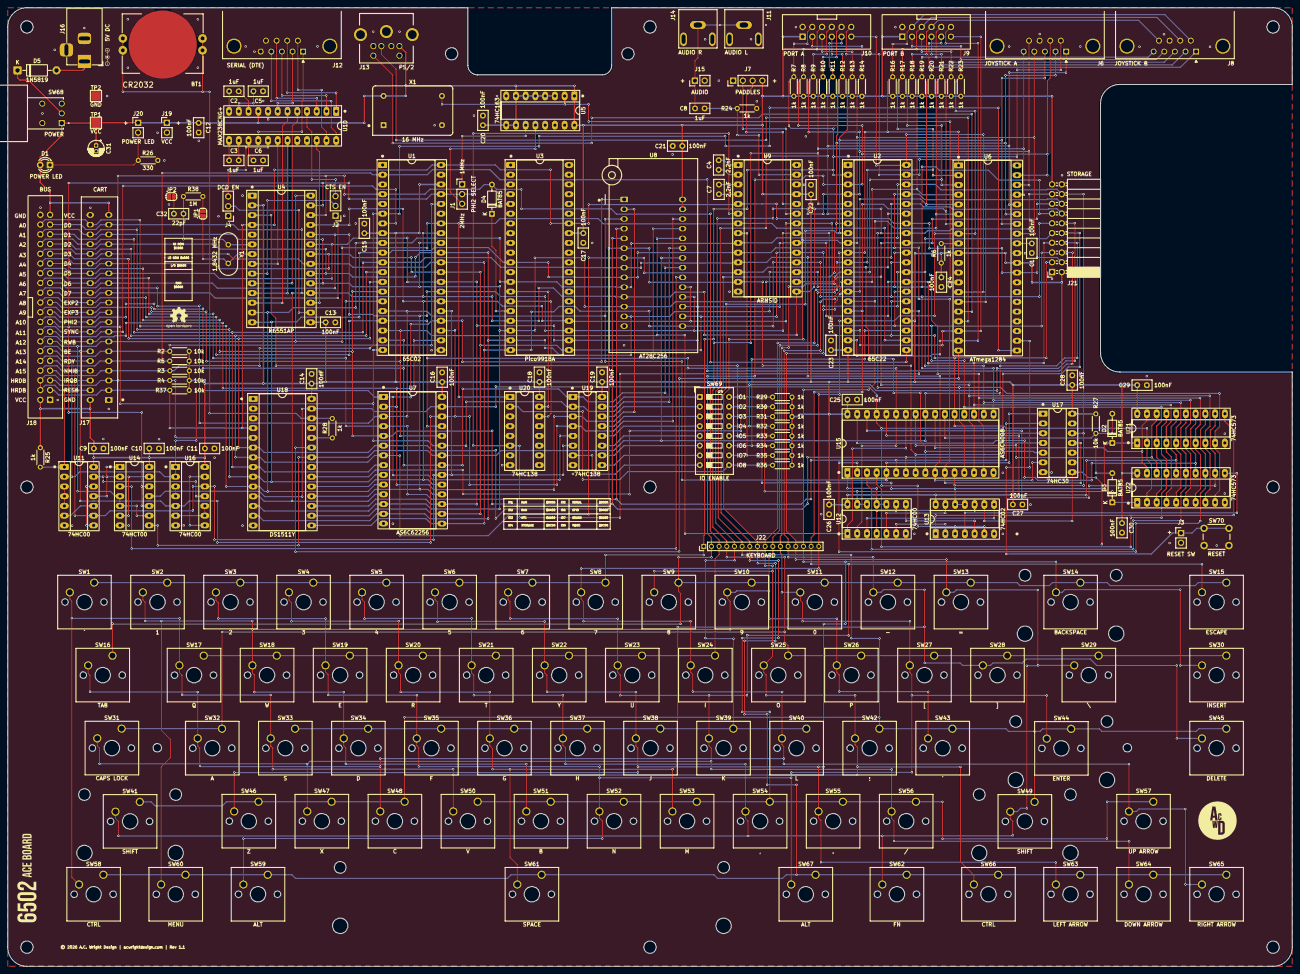
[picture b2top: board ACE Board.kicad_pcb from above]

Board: 2 copper layers, 335.0 x 250.0 mm, 205 parts (0 on the bottom side), 154 nets.

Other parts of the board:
CENTERPOS: Polarity_Center_Positive_6mm_SilkScreen
H1, H2, H2#2, H2#3, H2#4, H2#5, H2#6, H3#2, H4: MountingHole; MountingHole_3.2mm_M3
H3, H3#3: MountingHole; MountingHole_2.2mm_M2
